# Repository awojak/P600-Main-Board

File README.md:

# P600-Main-Board
Project of Main Board for P600. Design in KiCad.

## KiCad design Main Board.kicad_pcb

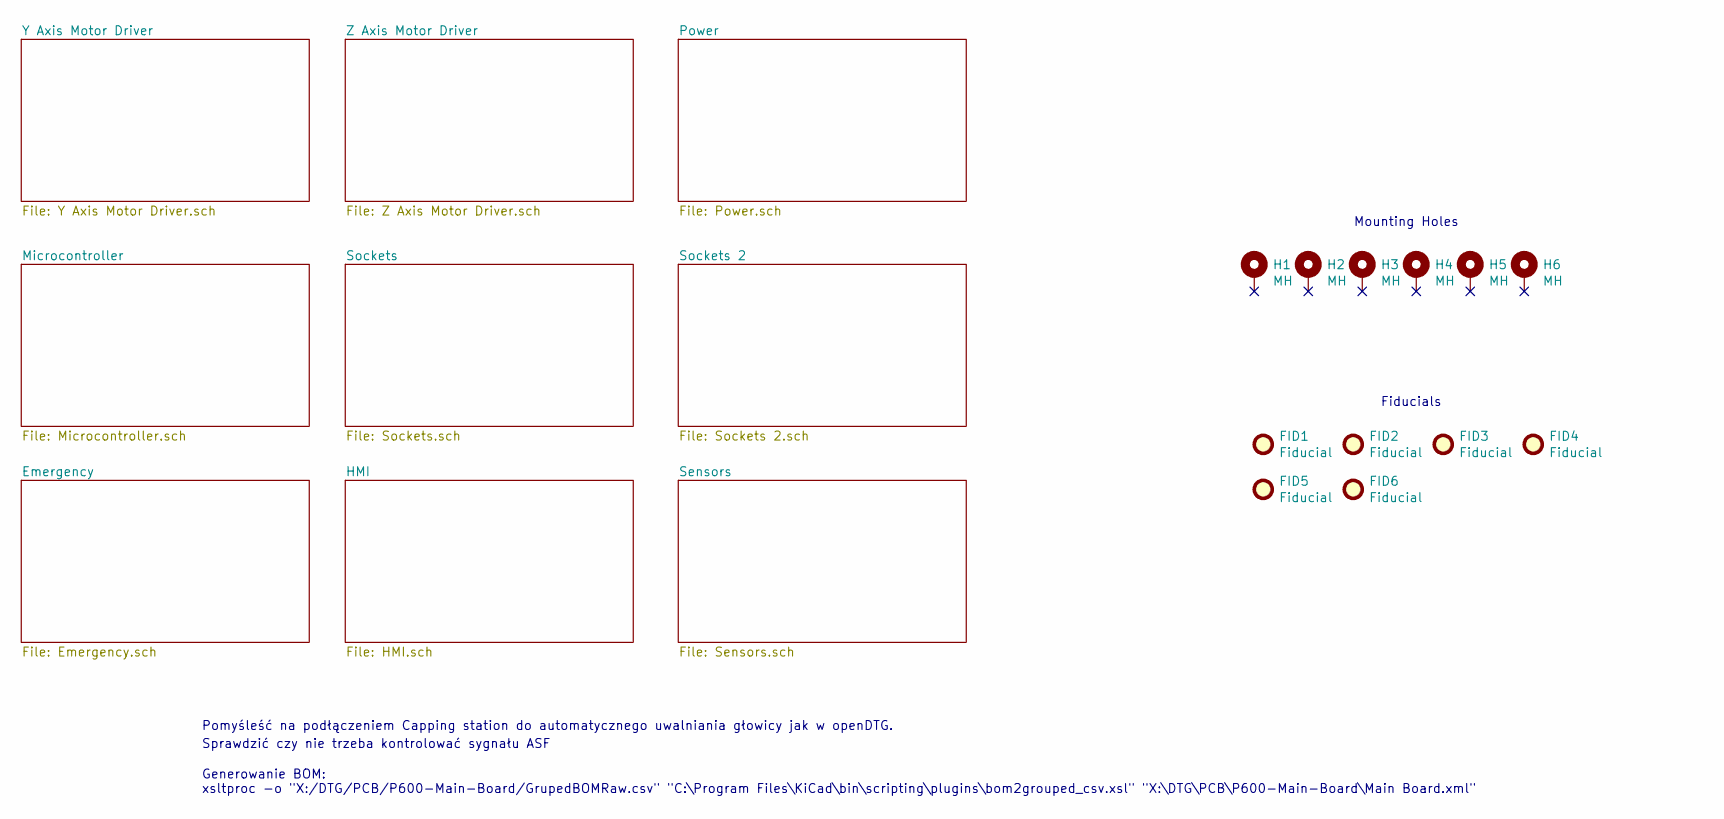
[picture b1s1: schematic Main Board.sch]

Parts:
FID1, FID2, FID3, FID4, FID5, FID6: Fiducial; Fiducial_1mm_Mask2mm
H1, H2, H3, H4, H5, H6: MH; MountingHole_3.5mm_Pad_Via

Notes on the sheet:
Pomyśleść na podłączeniem Capping station do automatycznego uwalniania głowicy jak w openDTG.
Sprawdzić czy nie trzeba kontrolować sygnału ASF
Mounting Holes
Fiducials
Generowanie BOM: xsltproc -o "X:/DTG/PCB/P600-Main-Board/GrupedBOMRaw.csv" "C:\Program Files\KiCad\bin\scripting\plugins\bom2grouped_csv.xsl" "X:\DTG\PCB\P600-Main-Board\Main Board.xml"

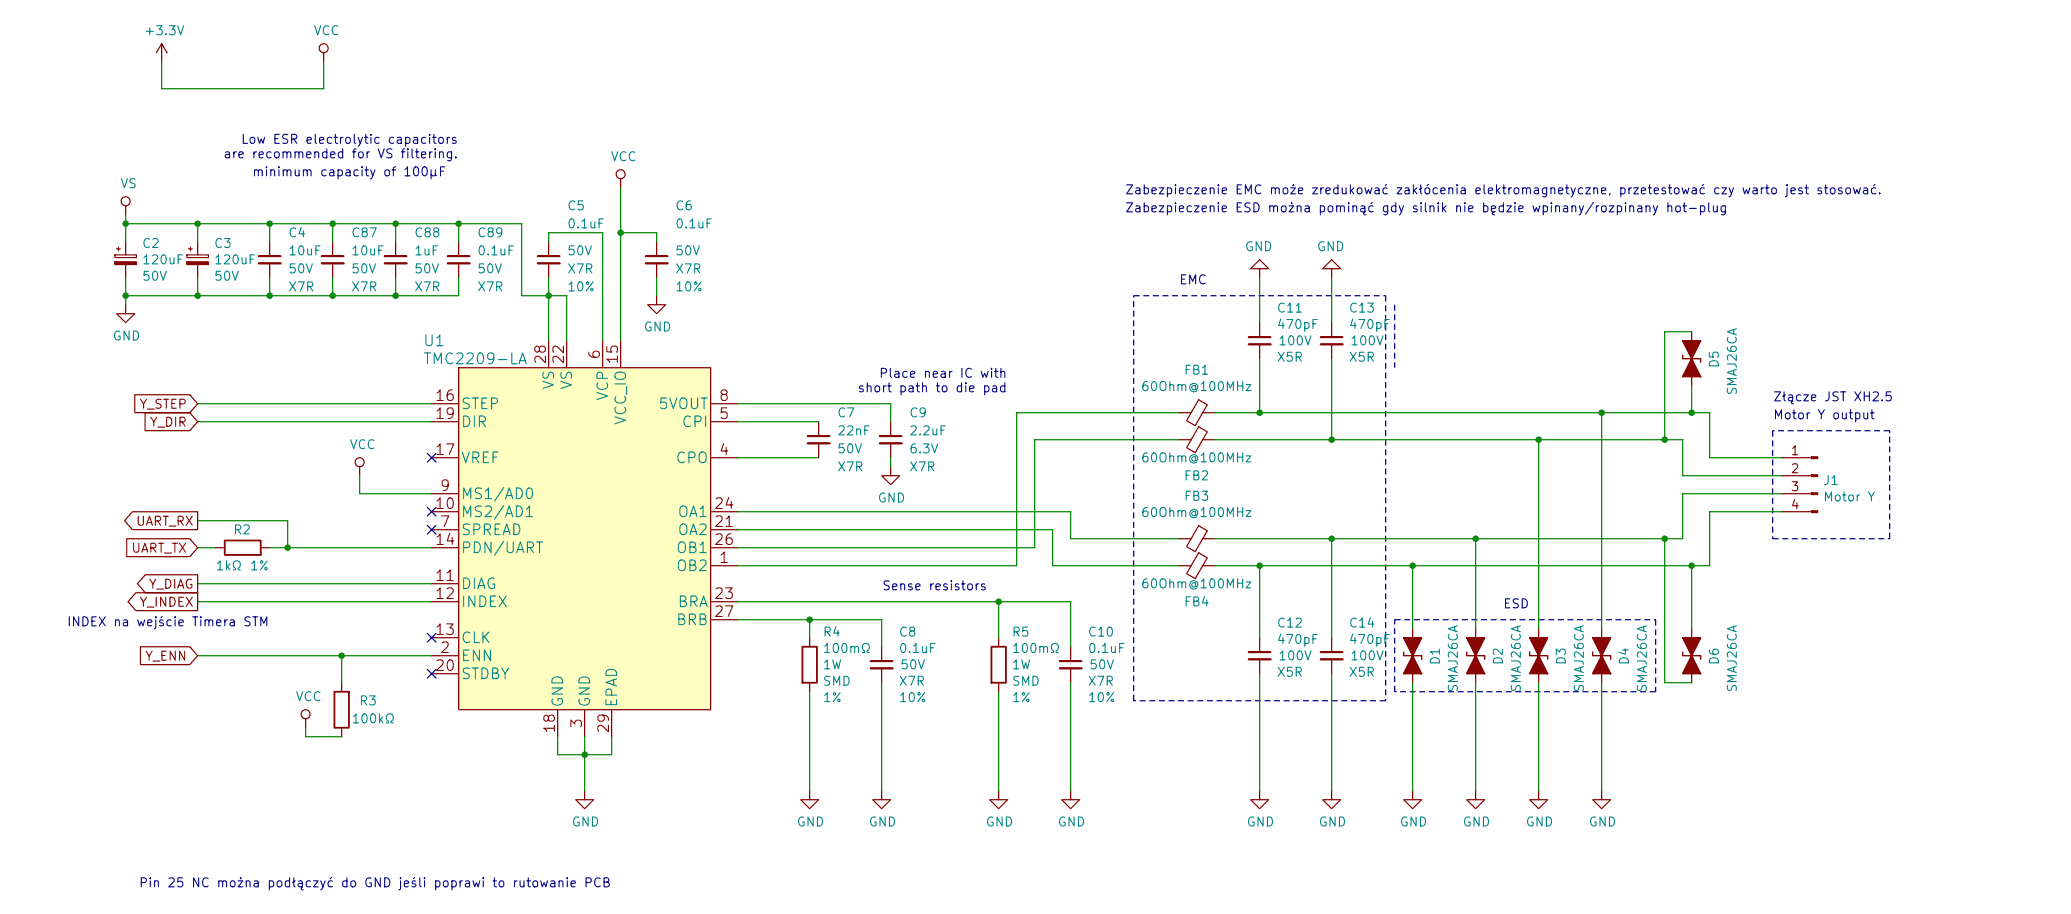
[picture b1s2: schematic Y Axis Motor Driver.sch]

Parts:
C2, C3: 120uF; CP_Radial_D8.0mm_P3.50mm; Tolerancja 20%
C4, C87: 10uF; C_1210_3225Metric; Tolerancja 10%
C5, C6, C8, C10, C89: 0.1uF; C_0603_1608Metric; Tolerancja 10%
C7: 22nF; C_0603_1608Metric; Tolerancja 10%
C9: 2.2uF; C_0603_1608Metric
C11, C12, C13, C14: 470pF; C_0805_2012Metric
C88: 1uF; C_0805_2012Metric; Tolerancja 10%
D1, D2, D3, D4, D5, D6: SMAJ26CA; D_SMA
FB1, FB2, FB3, FB4: 60Ohm@100MHz; L_0805_2012Metric
J1: Motor Y; JST_XH_B4B-XH-AM_1x04_P2.50mm_Vertical
R2: 1kΩ; R_0603_1608Metric; Tolerancja 1%
R3: 100kΩ; R_0603_1608Metric
R4, R5: 100mΩ; R_2010_5025Metric; Tolerancja 1%
U1: TMC2209-LA; QFN-28_5X5mm_P0.5mm_EP3.35x.3.35mm

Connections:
+3V3: C6.1, R3.1, U1.9 (MS1/AD0), U1.15 (VCC_IO); also elsewhere on the board
GND: C2.2, C3.2, C4.2, C6.2, C8.2, C9.2, C10.2, C11.1, C12.2, C13.1, C14.2, C87.2, C88.2, C89.2, D1.2 (A2), D2.2 (A2), D3.2 (A2), D4.2 (A2), R4.2, R5.2, U1.3 (GND), U1.18 (GND), U1.29 (EPAD); also elsewhere on the board
unnamed: C5.1, U1.6 (VCP)
unnamed: C7.1, U1.5 (CPI)
unnamed: C7.2, U1.4 (CPO)
unnamed: C8.1, R4.1, U1.27 (BRB)
unnamed: C9.1, U1.8 (5VOUT)
unnamed: C10.1, R5.1, U1.23 (BRA)
unnamed: C11.2, D4.1 (A1), D5.2 (A2), FB1.1, J1.1
unnamed: C12.1, D1.1 (A1), D6.1 (A1), FB4.1, J1.4
unnamed: C13.2, D3.1 (A1), D5.1 (A1), FB2.1, J1.2
unnamed: C14.1, D2.1 (A1), D6.2 (A2), FB3.1, J1.3
unnamed: FB1.2, U1.1 (OB2)
unnamed: FB2.2, U1.26 (OB1)
unnamed: FB3.2, U1.24 (OA1)
unnamed: FB4.2, U1.21 (OA2)
UART_RX: R2.2, U1.14 (PDN/UART); also elsewhere on the board
UART_TX: R2.1; also elsewhere on the board
VS: C2.1, C3.1, C4.1, C5.2, C87.1, C88.1, C89.1, U1.22 (VS), U1.28 (VS); also elsewhere on the board
Y_DIAG: U1.11 (DIAG); also elsewhere on the board
Y_DIR: U1.19 (DIR); also elsewhere on the board
Y_ENN: R3.2, U1.2 (ENN); also elsewhere on the board
Y_INDEX: U1.12 (INDEX); also elsewhere on the board
Y_STEP: U1.16 (STEP); also elsewhere on the board

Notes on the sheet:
Sense resistors
minimum capacity of 100μF
EMC
Motor Y output
Złącze JST XH2.5
Zabezpieczenie ESD można pominąć gdy silnik nie będzie wpinany/rozpinany hot-plug
Zabezpieczenie EMC może zredukować zakłócenia elektromagnetyczne, przetestować czy warto jest stosować.
Place near IC with short path to die pad
Low ESR electrolytic capacitors are recommended for VS filtering.
INDEX na wejście Timera STM
Pin 25 NC można podłączyć do GND jeśli poprawi to rutowanie PCB
ESD

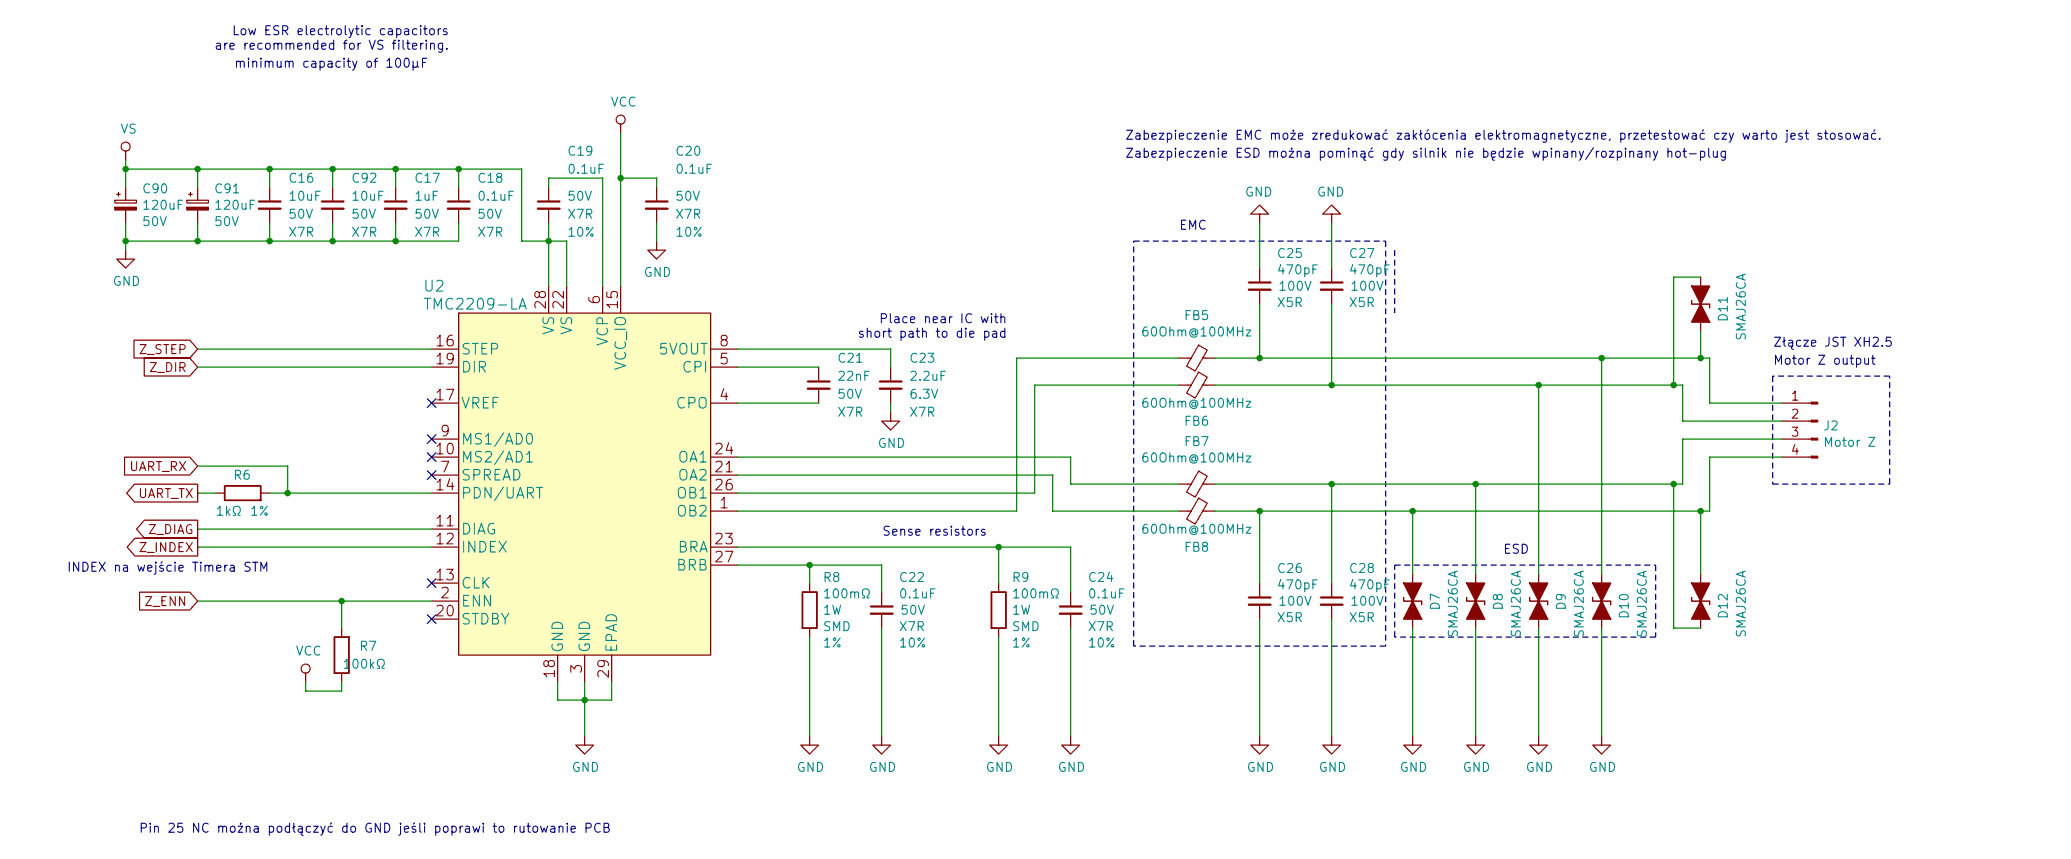
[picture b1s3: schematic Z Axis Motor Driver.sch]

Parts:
C16, C92: 10uF; C_1210_3225Metric; Tolerancja 10%
C17: 1uF; C_0805_2012Metric; Tolerancja 10%
C18, C19, C20, C22, C24: 0.1uF; C_0603_1608Metric; Tolerancja 10%
C21: 22nF; C_0603_1608Metric; Tolerancja 10%
C23: 2.2uF; C_0603_1608Metric
C25, C26, C27, C28: 470pF; C_0805_2012Metric
C90, C91: 120uF; CP_Radial_D8.0mm_P3.50mm; Tolerancja 20%
D7, D8, D9, D10, D11, D12: SMAJ26CA; D_SMA
FB5, FB6, FB7, FB8: 60Ohm@100MHz; L_0805_2012Metric
J2: Motor Z; JST_XH_B4B-XH-AM_1x04_P2.50mm_Vertical
R6: 1kΩ; R_0603_1608Metric; Tolerancja 1%
R7: 100kΩ; R_0603_1608Metric
R8, R9: 100mΩ; R_2010_5025Metric; Tolerancja 1%
U2: TMC2209-LA; QFN-28_5X5mm_P0.5mm_EP3.35x.3.35mm

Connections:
+3V3: C20.1, R7.1, U2.15 (VCC_IO); also elsewhere on the board
GND: C16.2, C17.2, C18.2, C20.2, C22.2, C23.2, C24.2, C25.1, C26.2, C27.1, C28.2, C90.2, C91.2, C92.2, D7.2 (A2), D8.2 (A2), D9.2 (A2), D10.2 (A2), R8.2, R9.2, U2.3 (GND), U2.18 (GND), U2.29 (EPAD); also elsewhere on the board
unnamed: C19.1, U2.6 (VCP)
unnamed: C21.1, U2.5 (CPI)
unnamed: C21.2, U2.4 (CPO)
unnamed: C22.1, R8.1, U2.27 (BRB)
unnamed: C23.1, U2.8 (5VOUT)
unnamed: C24.1, R9.1, U2.23 (BRA)
unnamed: C25.2, D10.1 (A1), D11.2 (A2), FB5.1, J2.1
unnamed: C26.1, D7.1 (A1), D12.1 (A1), FB8.1, J2.4
unnamed: C27.2, D9.1 (A1), D11.1 (A1), FB6.1, J2.2
unnamed: C28.1, D8.1 (A1), D12.2 (A2), FB7.1, J2.3
unnamed: FB5.2, U2.1 (OB2)
unnamed: FB6.2, U2.26 (OB1)
unnamed: FB7.2, U2.24 (OA1)
unnamed: FB8.2, U2.21 (OA2)
UART_RX: R6.2, U2.14 (PDN/UART); also elsewhere on the board
UART_TX: R6.1; also elsewhere on the board
VS: C16.1, C17.1, C18.1, C19.2, C90.1, C91.1, C92.1, U2.22 (VS), U2.28 (VS); also elsewhere on the board
Z_DIAG: U2.11 (DIAG); also elsewhere on the board
Z_DIR: U2.19 (DIR); also elsewhere on the board
Z_ENN: R7.2, U2.2 (ENN); also elsewhere on the board
Z_INDEX: U2.12 (INDEX); also elsewhere on the board
Z_STEP: U2.16 (STEP); also elsewhere on the board

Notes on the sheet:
Sense resistors
minimum capacity of 100μF
EMC
Motor Z output
Złącze JST XH2.5
Zabezpieczenie ESD można pominąć gdy silnik nie będzie wpinany/rozpinany hot-plug
Zabezpieczenie EMC może zredukować zakłócenia elektromagnetyczne, przetestować czy warto jest stosować.
Place near IC with short path to die pad
Low ESR electrolytic capacitors are recommended for VS filtering.
INDEX na wejście Timera STM
Pin 25 NC można podłączyć do GND jeśli poprawi to rutowanie PCB
ESD

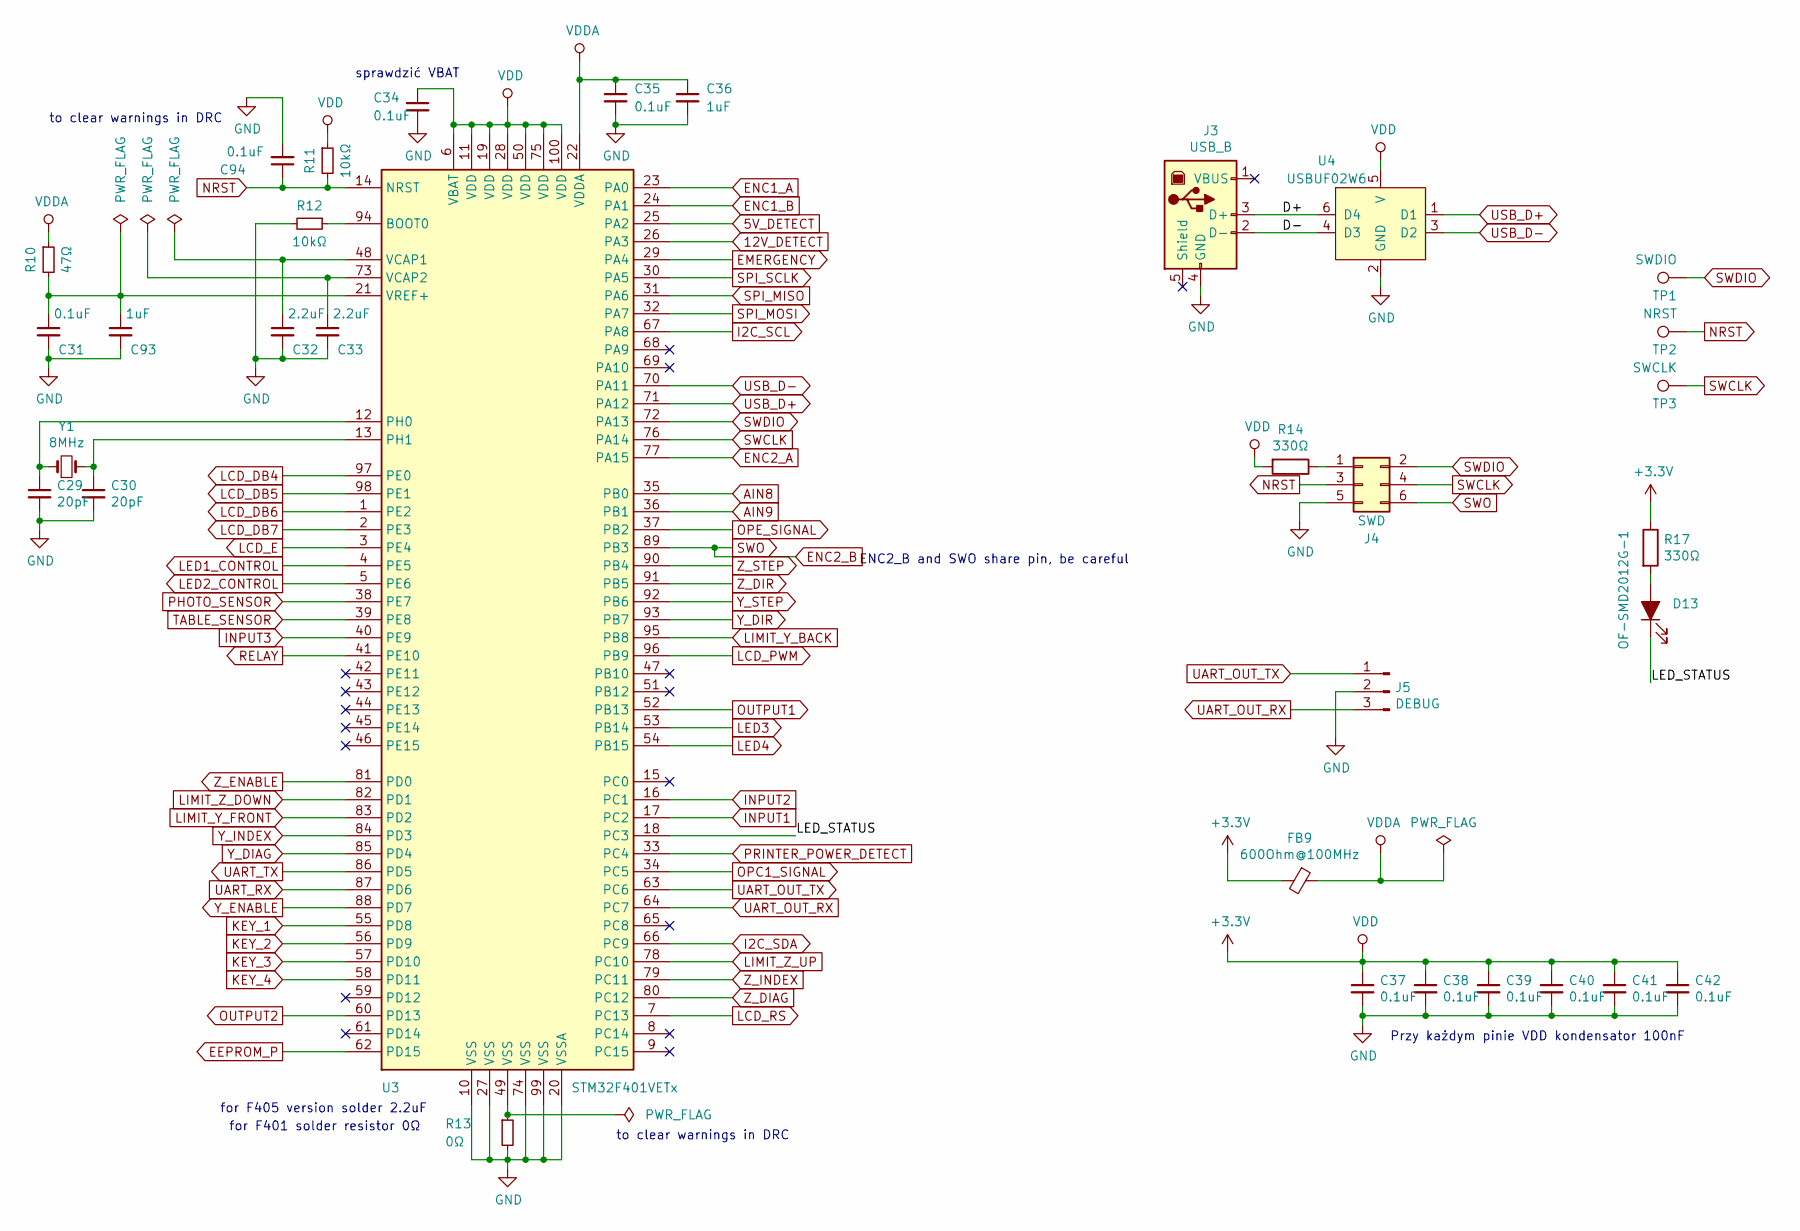
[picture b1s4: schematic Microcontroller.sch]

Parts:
C29, C30: 20pF; C_0603_1608Metric
C31, C34, C35, C37, C38, C39, C40, C41, C42, C94: 0.1uF; C_0603_1608Metric; Tolerancja 10%
C32, C33: 2.2uF; C_0603_1608Metric
C36: 1uF; C_0603_1608Metric; Tolerancja 10%
C93: 1uF; C_0603_1608Metric
D13: OF-SMD2012G-1; D_0805_2012Metric
FB9: 600Ohm@100MHz; L_0603_1608Metric
J3: USB_B; USB_B_TE_5787834_Vertical
J4: SWD; Tag-Connect_TC2030-IDC-NL_2x03_P1.27mm_Vertical
J5: DEBUG; JST_PH_B3B-PH-K_1x03_P2.00mm_Vertical
R10: 47Ω; R_0603_1608Metric
R11, R12: 10kΩ; R_0603_1608Metric
R13: 0Ω; R_0603_1608Metric
R14, R17: 330Ω; R_0603_1608Metric
TP1: SWDIO; TestPoint_Pad_D1.5mm
TP2: NRST; TestPoint_Pad_D1.5mm
TP3: SWCLK; TestPoint_Pad_D1.5mm
U3: STM32F401VETx; LQFP-100_14x14mm_P0.5mm
U4: USBUF02W6; SOT323-6L
Y1: 8MHz; Crystal_HC49-4H_Vertical

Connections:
5V_DETECT: U3.25 (PA2); also elsewhere on the board
12V_DETECT: U3.26 (PA3); also elsewhere on the board
+3V3: C34.1, C37.1, C38.1, C39.1, C40.1, C41.1, C42.1, FB9.2, R11.1, R14.2, R17.1, U3.6 (VBAT), U3.11 (VDD), U3.19 (VDD), U3.28 (VDD), U3.50 (VDD), U3.75 (VDD), U3.100 (VDD), U4.5 (V); also elsewhere on the board
/Microcontroller/D+: J3.3 (D+), U4.6 (D4)
/Microcontroller/D-: J3.2 (D-), U4.4 (D3)
/Microcontroller/LED_STATUS: D13.1 (K), U3.18 (PC3)
AIN8: U3.35 (PB0); also elsewhere on the board
AIN9: U3.36 (PB1); also elsewhere on the board
EEPROM_P: U3.62 (PD15); also elsewhere on the board
EMERGENCY: U3.29 (PA4); also elsewhere on the board
ENC1_A: U3.23 (PA0); also elsewhere on the board
ENC1_B: U3.24 (PA1); also elsewhere on the board
ENC2_A: U3.77 (PA15); also elsewhere on the board
ENC2_B: J4.6, U3.89 (PB3); also elsewhere on the board
GND: C29.2, C30.2, C31.2, C32.2, C33.2, C34.2, C35.2, C36.2, C37.2, C38.2, C39.2, C40.2, C41.2, C42.2, C93.2, C94.2, J3.4 (GND), J4.5, J5.2, R12.2, R13.2, U3.10 (VSS), U3.20 (VSSA), U3.27 (VSS), U3.74 (VSS), U3.99 (VSS), U4.2 (GND); also elsewhere on the board
I2C_SCL: U3.67 (PA8); also elsewhere on the board
I2C_SDA: U3.66 (PC9); also elsewhere on the board
INPUT1: U3.17 (PC2); also elsewhere on the board
INPUT2: U3.16 (PC1); also elsewhere on the board
INPUT3: U3.40 (PE9); also elsewhere on the board
KEY_1: U3.55 (PD8); also elsewhere on the board
KEY_2: U3.56 (PD9); also elsewhere on the board
KEY_3: U3.57 (PD10); also elsewhere on the board
KEY_4: U3.58 (PD11); also elsewhere on the board
LCD_DB4: U3.97 (PE0); also elsewhere on the board
LCD_DB5: U3.98 (PE1); also elsewhere on the board
LCD_DB6: U3.1 (PE2); also elsewhere on the board
LCD_DB7: U3.2 (PE3); also elsewhere on the board
LCD_E: U3.3 (PE4); also elsewhere on the board
LCD_PWM: U3.96 (PB9); also elsewhere on the board
LCD_RS: U3.7 (PC13); also elsewhere on the board
LED1_CONTROL: U3.4 (PE5); also elsewhere on the board
LED2_CONTROL: U3.5 (PE6); also elsewhere on the board
LED3: U3.53 (PB14); also elsewhere on the board
LED4: U3.54 (PB15); also elsewhere on the board
LIMIT_Y_BACK: U3.95 (PB8); also elsewhere on the board
LIMIT_Y_FRONT: U3.83 (PD2); also elsewhere on the board
LIMIT_Z_DOWN: U3.82 (PD1); also elsewhere on the board
LIMIT_Z_UP: U3.78 (PC10); also elsewhere on the board
NRST: C94.1, J4.3, R11.2, TP2.1, U3.14 (NRST)
unnamed: C29.1, U3.12 (PH0), Y1.1
unnamed: C30.1, U3.13 (PH1), Y1.2
unnamed: C31.1, C93.1, R10.2, U3.21 (VREF+)
unnamed: C32.1, U3.48 (VCAP1)
unnamed: C33.1, U3.73 (VCAP2)
unnamed: D13.2 (A), R17.2
unnamed: J4.1, R14.1
unnamed: R12.1, U3.94 (BOOT0)
unnamed: R13.1, U3.49 (VSS)
OPC1_SIGNAL: U3.34 (PC5); also elsewhere on the board
OPE_SIGNAL: U3.37 (PB2); also elsewhere on the board
OUTPUT1: U3.52 (PB13); also elsewhere on the board
OUTPUT2: U3.60 (PD13); also elsewhere on the board
PHOTO_SENSOR: U3.38 (PE7); also elsewhere on the board
PRINTER_POWER_DETECT: U3.33 (PC4); also elsewhere on the board
RELAY: U3.41 (PE10); also elsewhere on the board
SPI_MISO: U3.31 (PA6); also elsewhere on the board
SPI_MOSI: U3.32 (PA7); also elsewhere on the board
SPI_SCLK: U3.30 (PA5); also elsewhere on the board
SWCLK: J4.4, TP3.1, U3.76 (PA14)
SWDIO: J4.2, TP1.1, U3.72 (PA13)
TABLE_SENSOR: U3.39 (PE8); also elsewhere on the board
UART_OUT_RX: J5.3, U3.64 (PC7)
UART_OUT_TX: J5.1, U3.63 (PC6)
UART_RX: U3.87 (PD6); also elsewhere on the board
UART_TX: U3.86 (PD5); also elsewhere on the board
USB_D+: U3.71 (PA12), U4.1 (D1)
USB_D-: U3.70 (PA11), U4.3 (D2)
VDDA: C35.1, C36.1, FB9.1, R10.1, U3.22 (VDDA)
Y_DIAG: U3.85 (PD4); also elsewhere on the board
Y_DIR: U3.93 (PB7); also elsewhere on the board
Y_ENABLE: U3.88 (PD7); also elsewhere on the board
Y_INDEX: U3.84 (PD3); also elsewhere on the board
Y_STEP: U3.92 (PB6); also elsewhere on the board
Z_DIAG: U3.80 (PC12); also elsewhere on the board
Z_DIR: U3.91 (PB5); also elsewhere on the board
Z_ENABLE: U3.81 (PD0); also elsewhere on the board
Z_INDEX: U3.79 (PC11); also elsewhere on the board
Z_STEP: U3.90 (PB4); also elsewhere on the board

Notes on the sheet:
for F405 version solder 2.2uF
for F401 solder resistor 0Ω
Przy każdym pinie VDD kondensator 100nF
sprawdzić VBAT
ENC2_B and SWO share pin, be careful
to clear warnings in DRC

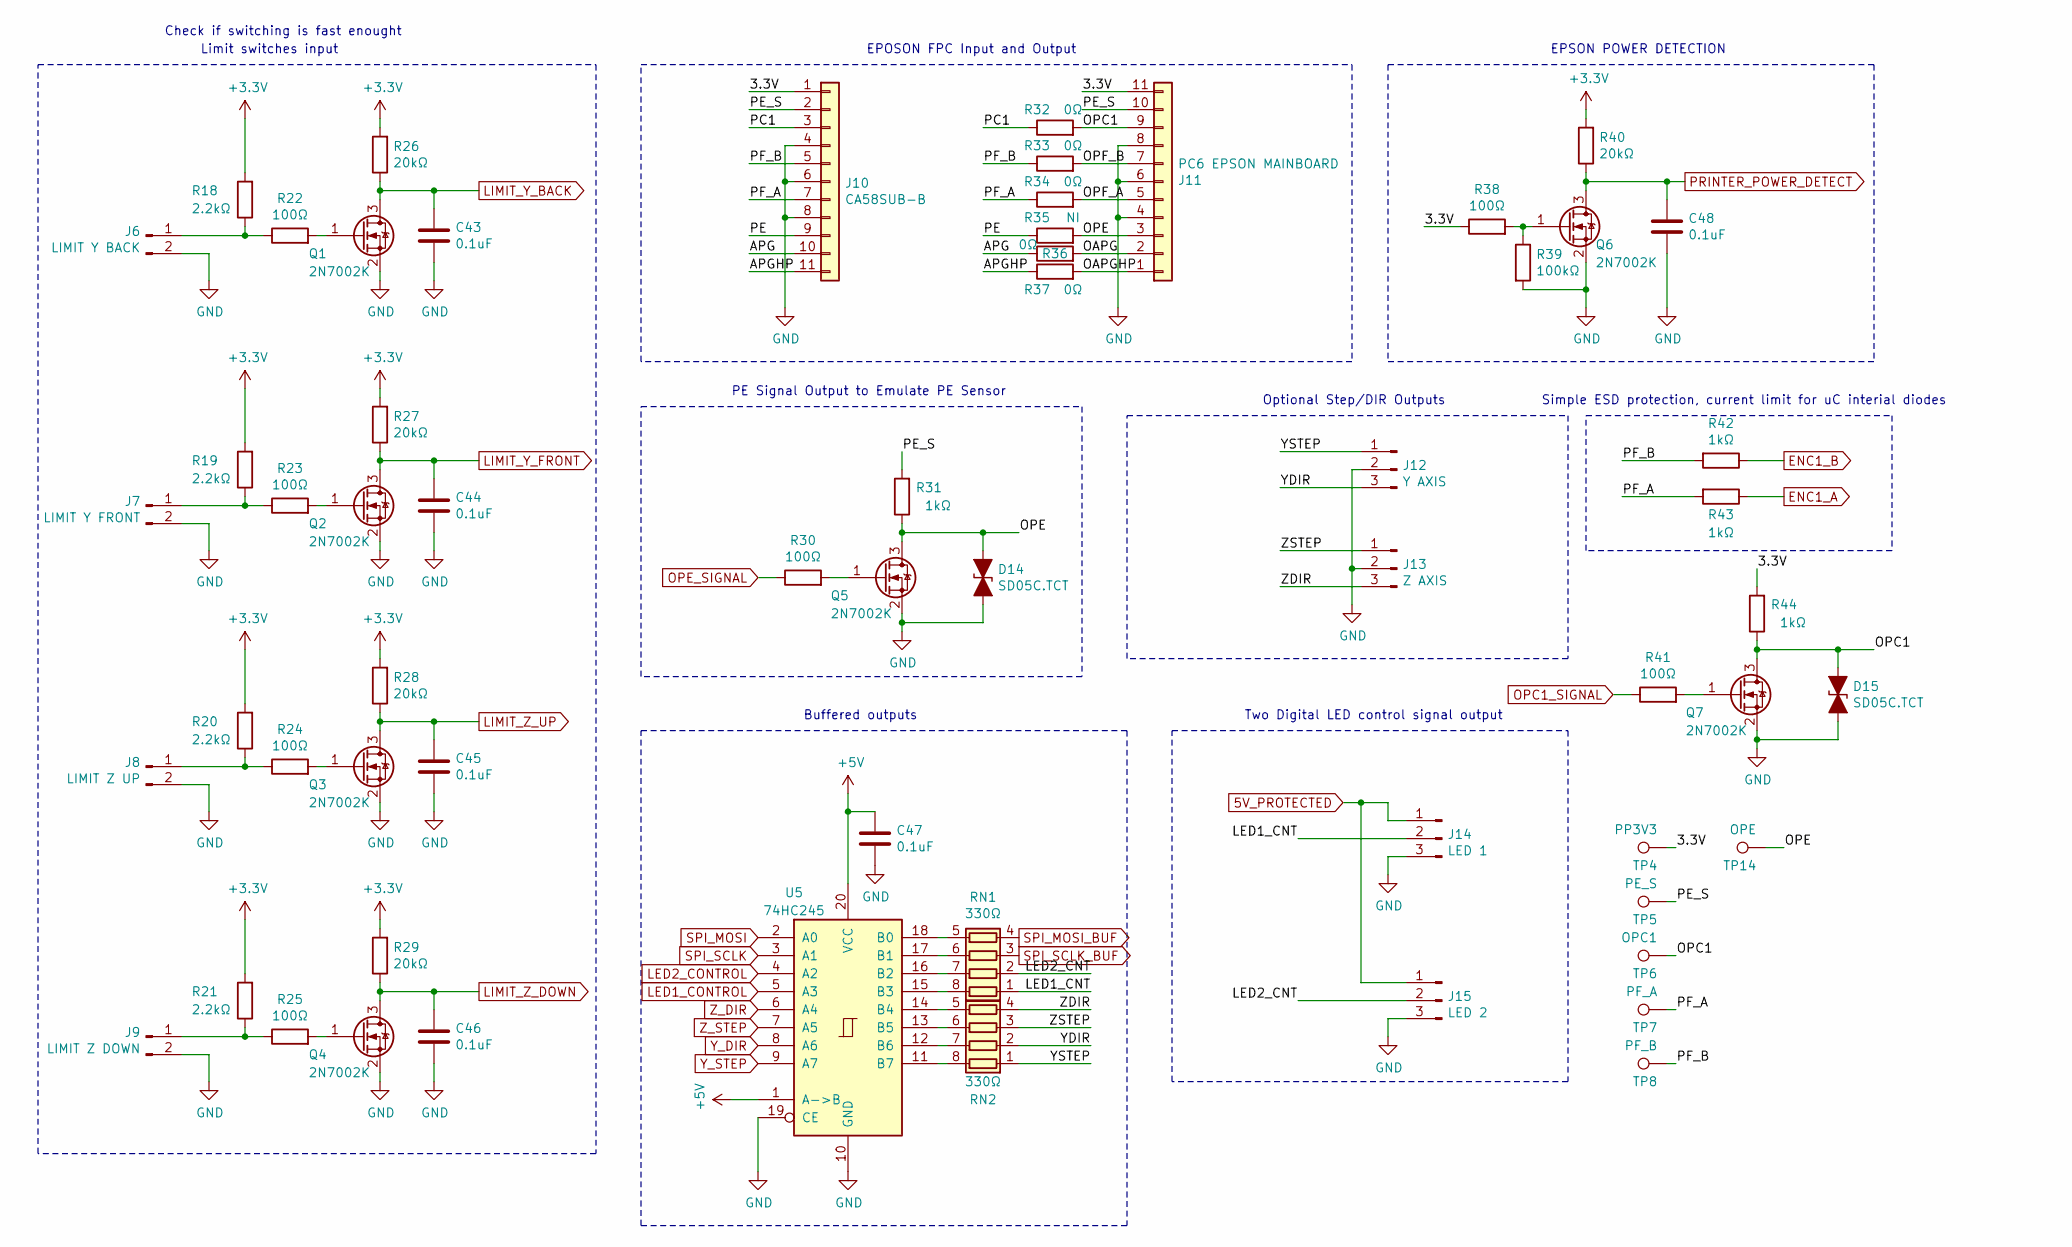
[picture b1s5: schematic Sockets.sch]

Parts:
C43, C44, C45, C46, C48: 0.1uF; C_0603_1608Metric
C47: 0.1uF; C_0603_1608Metric; Tolerancja 10%
D14, D15: SD05C.TCT; D_SOD-323
J6: LIMIT Y BACK; JST_PH_B2B-PH-K_1x02_P2.00mm_Vertical
J7: LIMIT Y FRONT; JST_PH_B2B-PH-K_1x02_P2.00mm_Vertical
J8: LIMIT Z UP; JST_PH_B2B-PH-K_1x02_P2.00mm_Vertical
J9: LIMIT Z DOWN; JST_PH_B2B-PH-K_1x02_P2.00mm_Vertical
J10: CA58SUB-B; THT_FPC_r1.0mm_11pin_vertical
J11: PC6 EPSON MAINBOARD; THT_FPC_r1.0mm_11pin_vertical
J12: Y AXIS; JST_PH_B3B-PH-K_1x03_P2.00mm_Vertical
J13: Z AXIS; JST_PH_B3B-PH-K_1x03_P2.00mm_Vertical
J14: LED 1; JST_PH_B3B-PH-K_1x03_P2.00mm_Vertical
J15: LED 2; JST_PH_B3B-PH-K_1x03_P2.00mm_Vertical
Q1, Q2, Q3, Q4, Q5, Q6, Q7: 2N7002K; SOT-23
R18, R19, R20, R21: 2.2kΩ; R_0603_1608Metric
R22, R23, R24, R25, R30, R38, R41: 100Ω; R_0603_1608Metric
R26, R27, R28, R29, R40: 20kΩ; R_0603_1608Metric
R31, R42, R43, R44: 1kΩ; R_0603_1608Metric
R32, R33, R34, R36, R37: 0Ω; R_0603_1608Metric
R35: NI; R_0603_1608Metric
R39: 100kΩ; R_0603_1608Metric
RN1, RN2: 330Ω; R_Array_Convex_4x0603
TP4: PP3V3; TestPoint_Pad_D1.5mm
TP5: PE_S; TestPoint_Pad_D1.5mm
TP6: OPC1; TestPoint_Pad_D1.5mm
TP7: PF_A; TestPoint_Pad_D1.5mm
TP8: PF_B; TestPoint_Pad_D1.5mm
TP14: OPE; TestPoint_Pad_D1.5mm
U5: 74HC245; TSSOP-20_4.4x6.5mm_P0.65mm

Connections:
5V_PROTECTED: J14.1, J15.1; also elsewhere on the board
+3V3: R18.2, R19.2, R20.2, R21.2, R26.2, R27.2, R28.2, R29.2, R40.2; also elsewhere on the board
+5V: C47.1, U5.1 (A->B), U5.20 (VCC); also elsewhere on the board
/Sockets/3.3V: J10.1, J11.11, R38.1, R44.2, TP4.1
/Sockets/APG: J10.10, R36.1
/Sockets/APGHP: J10.11, R37.1
/Sockets/LED1_CNT: J14.2, RN1.1 (R1.1)
/Sockets/LED2_CNT: J15.2, RN1.2 (R2.1)
/Sockets/OAPG: J11.2, R36.2
/Sockets/OAPGHP: J11.1, R37.2
/Sockets/OPC1: D15.1 (A1), J11.9, Q7.3 (D), R32.2, R44.1, TP6.1
/Sockets/OPE: D14.1 (A1), J11.3, Q5.3 (D), R31.1, R35.2, TP14.1
/Sockets/OPF_A: J11.5, R34.2
/Sockets/OPF_B: J11.7, R33.2
/Sockets/PC1: J10.3, R32.1
/Sockets/PE: J10.9, R35.1
/Sockets/PE_S: J10.2, J11.10, R31.2, TP5.1
/Sockets/PF_A: J10.7, R34.1, R43.2, TP7.1
/Sockets/PF_B: J10.5, R33.1, R42.2, TP8.1
/Sockets/YDIR: J12.3, RN2.2 (R2.1)
/Sockets/YSTEP: J12.1, RN2.1 (R1.1)
/Sockets/ZDIR: J13.3, RN2.4 (R4.1)
/Sockets/ZSTEP: J13.1, RN2.3 (R3.1)
ENC1_A: R43.1; also elsewhere on the board
ENC1_B: R42.1; also elsewhere on the board
GND: C43.2, C44.2, C45.2, C46.2, C47.2, C48.2, D14.2 (A2), D15.2 (A2), J6.2, J7.2, J8.2, J9.2, J10.4, J10.6, J10.8, J11.4, J11.6, J11.8, J12.2, J13.2, J14.3, J15.3, Q1.2 (S), Q2.2 (S), Q3.2 (S), Q4.2 (S), Q5.2 (S), Q6.2 (S), Q7.2 (S), R39.2, U5.10 (GND), U5.19 (CE); also elsewhere on the board
LED1_CONTROL: U5.5 (A3); also elsewhere on the board
LED2_CONTROL: U5.4 (A2); also elsewhere on the board
LIMIT_Y_BACK: C43.1, Q1.3 (D), R26.1; also elsewhere on the board
LIMIT_Y_FRONT: C44.1, Q2.3 (D), R27.1; also elsewhere on the board
LIMIT_Z_DOWN: C46.1, Q4.3 (D), R29.1; also elsewhere on the board
LIMIT_Z_UP: C45.1, Q3.3 (D), R28.1; also elsewhere on the board
unnamed: J6.1, R18.1, R22.1
unnamed: J7.1, R19.1, R23.1
unnamed: J8.1, R20.1, R24.1
unnamed: J9.1, R21.1, R25.1
unnamed: Q1.1 (G), R22.2
unnamed: Q2.1 (G), R23.2
unnamed: Q3.1 (G), R24.2
unnamed: Q4.1 (G), R25.2
unnamed: Q5.1 (G), R30.2
unnamed: Q6.1 (G), R38.2, R39.1
unnamed: Q7.1 (G), R41.2
unnamed: RN1.5 (R4.2), U5.18 (B0)
unnamed: RN1.6 (R3.2), U5.17 (B1)
unnamed: RN1.7 (R2.2), U5.16 (B2)
unnamed: RN1.8 (R1.2), U5.15 (B3)
unnamed: RN2.5 (R4.2), U5.14 (B4)
unnamed: RN2.6 (R3.2), U5.13 (B5)
unnamed: RN2.7 (R2.2), U5.12 (B6)
unnamed: RN2.8 (R1.2), U5.11 (B7)
OPC1_SIGNAL: R41.1; also elsewhere on the board
OPE_SIGNAL: R30.1; also elsewhere on the board
PRINTER_POWER_DETECT: C48.1, Q6.3 (D), R40.1; also elsewhere on the board
SPI_MOSI: U5.2 (A0); also elsewhere on the board
SPI_MOSI_BUF: RN1.4 (R4.1); also elsewhere on the board
SPI_SCLK: U5.3 (A1); also elsewhere on the board
SPI_SCLK_BUF: RN1.3 (R3.1); also elsewhere on the board
Y_DIR: U5.8 (A6); also elsewhere on the board
Y_STEP: U5.9 (A7); also elsewhere on the board
Z_DIR: U5.6 (A4); also elsewhere on the board
Z_STEP: U5.7 (A5); also elsewhere on the board

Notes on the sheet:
Simple ESD protection, current limit for uC interial diodes
Limit switches input
Check if switching is fast enought
Two Digital LED control signal output
EPOSON FPC Input and Output
PE Signal Output to Emulate PE Sensor
Optional Step/DIR Outputs
EPSON POWER DETECTION
Buffered outputs

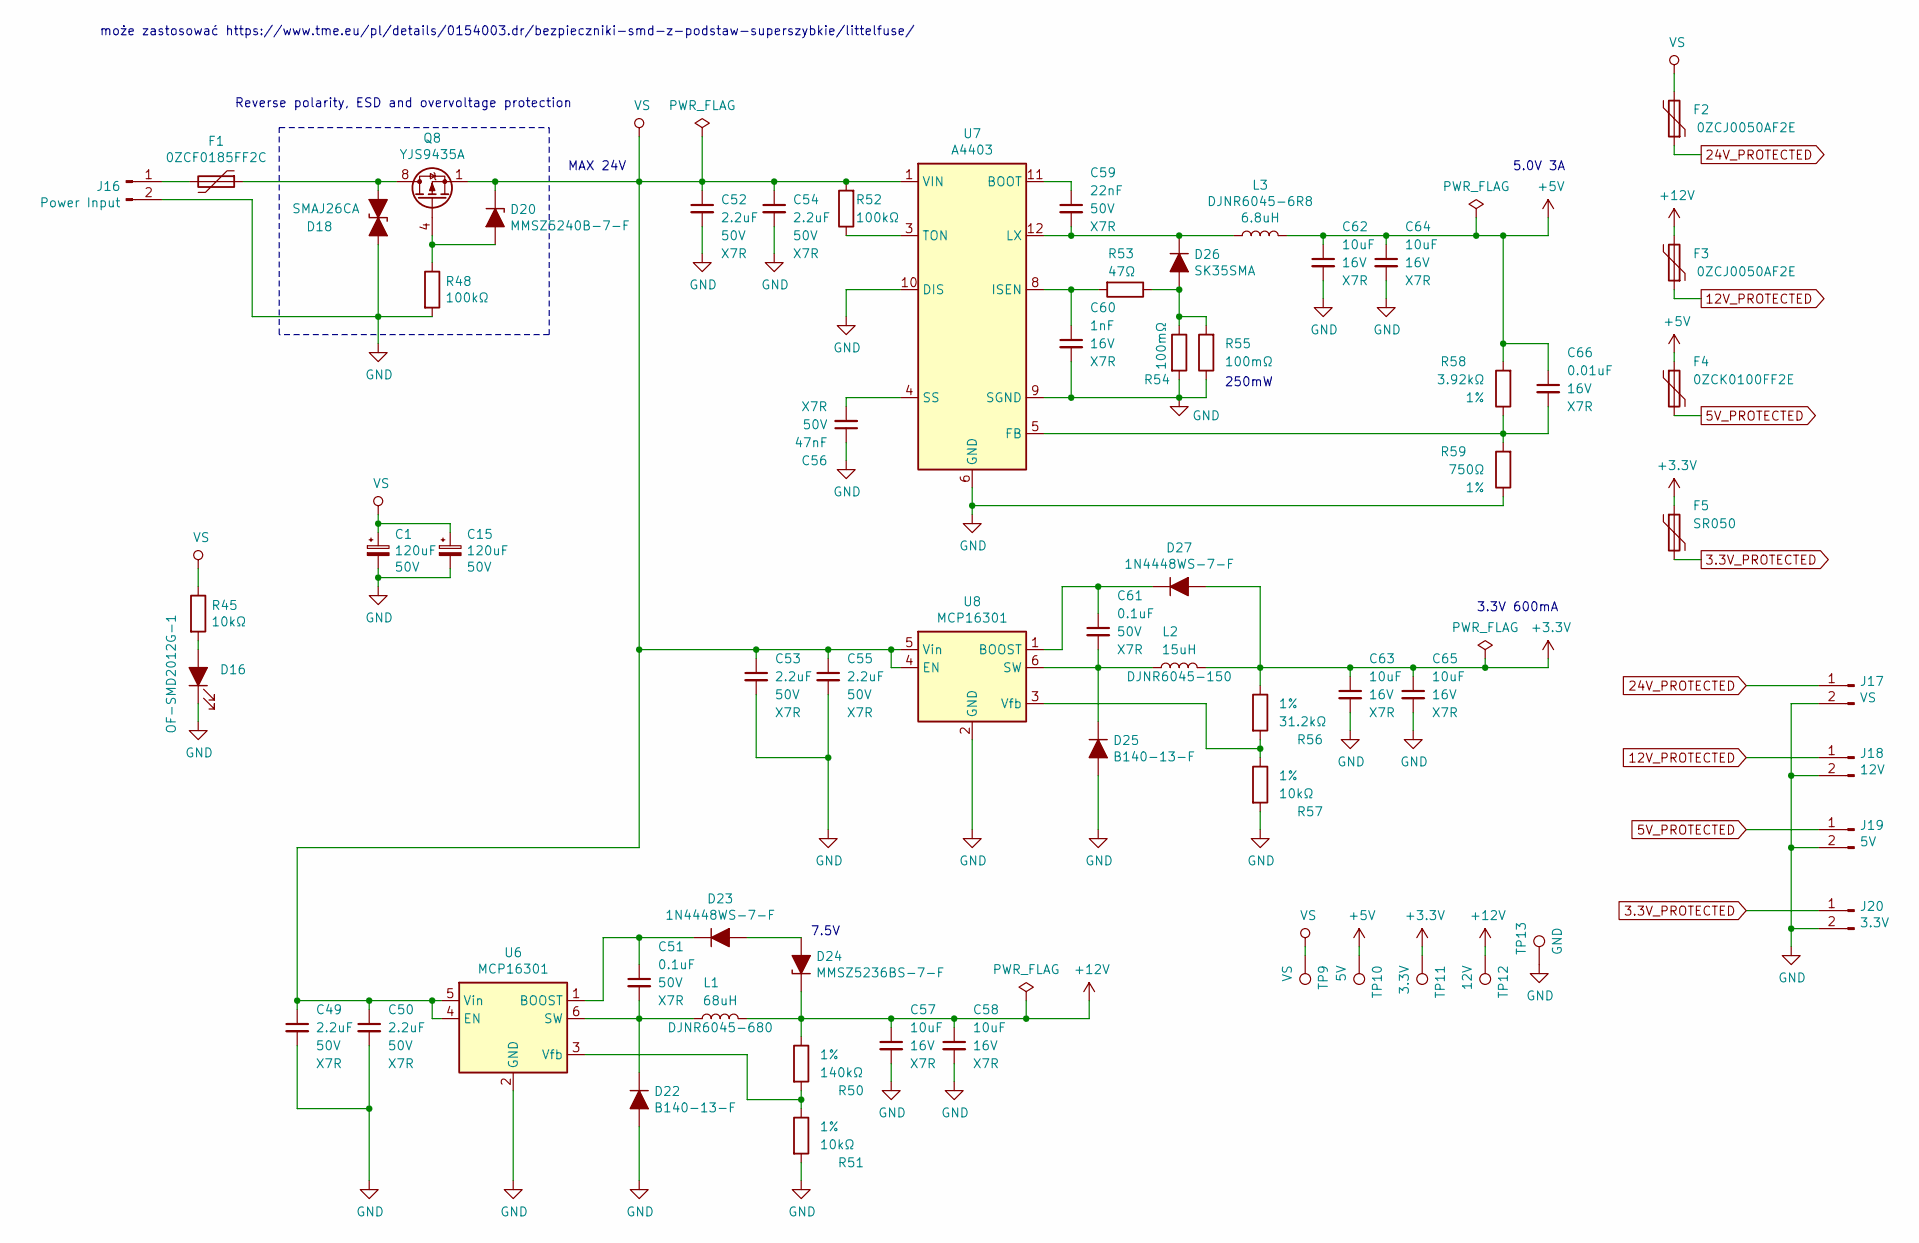
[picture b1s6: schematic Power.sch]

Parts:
C1, C15: 120uF; CP_Radial_D8.0mm_P3.50mm; Tolerancja 20%
C49, C50, C52, C53, C54, C55: 2.2uF; C_1206_3216Metric
C51, C61: 0.1uF; C_0603_1608Metric; Tolerancja 10%
C56: 47nF; C_0603_1608Metric
C57, C58, C62, C63, C64, C65: 10uF; C_1206_3216Metric; Tolerancja 10%
C59: 22nF; C_0603_1608Metric; Tolerancja 10%
C60: 1nF; C_0603_1608Metric
C66: 0.01uF; C_0603_1608Metric
D16: OF-SMD2012G-1; D_0805_2012Metric
D18: SMAJ26CA; D_SMA
D20: MMSZ5240B-7-F; D_SOD-123
D22, D25: B140-13-F; D_SMA
D23, D27: 1N4448WS-7-F; D_SOD-323
D24: MMSZ5236BS-7-F; D_SOD-323
D26: SK35SMA; D_SMA
F1: 0ZCF0185FF2C; Fuse_2920_7451Metric
F2, F3: 0ZCJ0050AF2E; Fuse_1206_3216Metric
F4: 0ZCK0100FF2E; Fuse_0805_2012Metric
F5: SR050; Fuse_0805_2012Metric
J16: Power Input; JST_XH_B2B-XH-AM_1x02_P2.50mm_Vertical
J17: VS; JST_PH_B2B-PH-K_1x02_P2.00mm_Vertical
J18: 12V; JST_PH_B2B-PH-K_1x02_P2.00mm_Vertical
J19: 5V; JST_PH_B2B-PH-K_1x02_P2.00mm_Vertical
J20: 3.3V; JST_PH_B2B-PH-K_1x02_P2.00mm_Vertical
L1: DJNR6045-680; L_6.2x6.2_H4.5
L2: DJNR6045-150; L_6.2x6.2_H4.5
L3: DJNR6045-6R8; L_6.2x6.2_H4.5
Q8: YJS9435A; SOP-8_3.9x4.9mm_P1.27mm
R45: 10kΩ; R_0805_2012Metric
R48, R52: 100kΩ; R_0603_1608Metric
R50: 140kΩ; R_0603_1608Metric; Tolerancja 1%
R51, R57: 10kΩ; R_0603_1608Metric; Tolerancja 1%
R53: 47Ω; R_0603_1608Metric
R54, R55: 100mΩ; R_1206_3216Metric
R56: 31.2kΩ; R_0603_1608Metric; Tolerancja 1%
R58: 3.92kΩ; R_0603_1608Metric; Tolerancja 1%
R59: 750Ω; R_0603_1608Metric; Tolerancja 1%
TP9: VS; TestPoint_Pad_D1.5mm
TP10: 5V; TestPoint_Pad_D1.5mm
TP11: 3.3V; TestPoint_Pad_D1.5mm
TP12: 12V; TestPoint_Pad_D1.5mm
TP13: GND; TestPoint_Pad_D1.5mm
U6, U8: MCP16301; SOT-23-6
U7: A4403; QFN-16-1EP_4x4mm_P0.65mm_EP2.7x2.7mm

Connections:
3.3V_PROTECTED: F5.2, J20.1; also elsewhere on the board
5V_PROTECTED: F4.2, J19.1; also elsewhere on the board
12V_PROTECTED: F3.1, J18.1; also elsewhere on the board
24V_PROTECTED: F2.1, J17.1; also elsewhere on the board
+3V3: C63.1, C65.1, D27.2 (A), F5.1, L2.2, R56.1, TP11.1; also elsewhere on the board
+5V: C62.1, C64.1, C66.1, F4.1, L3.2, R58.2, TP10.1; also elsewhere on the board
+12V: C57.1, C58.1, D24.1 (K), F3.2, L1.2, R50.1, TP12.1; also elsewhere on the board
GND: C1.2, C15.2, C49.2, C50.2, C52.2, C53.2, C54.2, C55.2, C56.1, C57.2, C58.2, C60.2, C62.2, C63.2, C64.2, C65.2, D16.1 (K), D18.1 (A1), D22.2 (A), D25.2 (A), J16.2, J17.2, J18.2, J19.2, J20.2, R48.2, R51.2, R54.2, R55.1, R57.2, R59.1, TP13.1, U6.2 (GND), U7.2 (GND), U7.6 (GND), U7.7 (GND), U7.9 (SGND), U7.10 (DIS), U7.13 (GND), U7.14 (GND), U7.15 (GND), U7.16 (GND), U7.17 (GND), U8.2 (GND); also elsewhere on the board
unnamed: C51.1, D23.1 (K), U6.1 (BOOST)
unnamed: C51.2, D22.1 (K), L1.1, U6.6 (SW)
unnamed: C56.2, U7.4 (SS)
unnamed: C59.1, U7.11 (BOOT)
unnamed: C59.2, D26.1 (K), L3.1, U7.12 (LX)
unnamed: C60.1, R53.2, U7.8 (ISEN)
unnamed: C61.1, D27.1 (K), U8.1 (BOOST)
unnamed: C61.2, D25.1 (K), L2.1, U8.6 (SW)
unnamed: C66.2, R58.1, R59.2, U7.5 (FB)
unnamed: D16.2 (A), R45.2
unnamed: D18.2 (A2), F1.1, Q8.5 (D), Q8.6 (D), Q8.7 (D), Q8.8 (D)
unnamed: D20.2 (A), Q8.4 (G), R48.1
unnamed: D23.2 (A), D24.2 (A)
unnamed: D26.2 (A), R53.1, R54.1, R55.2
unnamed: F1.2, J16.1
unnamed: R50.2, R51.1, U6.3 (Vfb)
unnamed: R52.1, U7.3 (TON)
unnamed: R56.2, R57.1, U8.3 (Vfb)
VS: C1.1, C15.1, C49.1, C50.1, C52.1, C53.1, C54.1, C55.1, D20.1 (K), F2.2, Q8.1 (S), Q8.2 (S), Q8.3 (S), R45.1, R52.2, TP9.1, U6.4 (EN), U6.5 (Vin), U7.1 (VIN), U8.4 (EN), U8.5 (Vin); also elsewhere on the board

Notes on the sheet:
5.0V 3A
250mW
3.3V 600mA
Reverse polarity, ESD and overvoltage protection
może zastosować https://www.tme.eu/pl/details/0154003.dr/bezpieczniki-smd-z-podstaw-superszybkie/littelfuse/
7.5V
MAX 24V
